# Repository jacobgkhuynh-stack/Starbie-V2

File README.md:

Hiya, this is for Half Life week 1 it's a Starbie: basically a desktop Tamagotchi but I made it into a compact rectangle creatively named the Starbie V2. How a Starbie works is it's basically the same thing as a Tamagotchi but you can tilt and move it to also interact with it.
So it has a 0.96in 128x64 oled display, a XIAO-ESP32-C3 as the brain, a DHT11 for temp and humidity sensing, and a MPU6050 for motion tracking.

Here's my BoMs
 Part | What it's for | Qty | Unit | Total | Vendor |
| --- | --- | --- | --- | --- | --- |
| [XIAO ESP32-C3](https://www.aliexpress.us/item/3256808627180483.html?spm=a2g0o.productlist.main.48.e3a850f6qPDWIA&algo_pvid=2e0f51a2-6e46-4c0e-9cd4-9e7c8a9bc2bc&algo_exp_id=2e0f51a2-6e46-4c0e-9cd4-9e7c8a9bc2bc-45&pdp_ext_f=%7B%22order%22%3A%22425%22%2C%22eval%22%3A%221%22%2C%22fromPage%22%3A%22search%22%7D&pdp_npi=6%40dis%21USD%2133.87%219.42%21%21%21225.63%2162.75%21%402101ca8b17917712554883951e117a%2112000046840040808%21sea%21US%210%21ABX%211%210%21n_tag%3A-29910%3Bd%3A92917014%3Bm03_new_user%3A-29895%3BpisId%3A5000000218165385&curPageLogUid=uNjXBfIDAfCY&utparam-url=scene%3Asearch%7Cquery_from%3A%7Cx_object_id%3A1005008813495235%7C_p_origin_prod%3A) | Dev board | 1 | $10.26 | $10.26 | [ANSIKI IoT Store](https://www.aliexpress.us/item/3256808627180483.html?spm=a2g0o.productlist.main.48.e3a850f6qPDWIA&algo_pvid=2e0f51a2-6e46-4c0e-9cd4-9e7c8a9bc2bc&algo_exp_id=2e0f51a2-6e46-4c0e-9cd4-9e7c8a9bc2bc-45&pdp_ext_f=%7B%22order%22%3A%22425%22%2C%22eval%22%3A%221%22%2C%22fromPage%22%3A%22search%22%7D&pdp_npi=6%40dis%21USD%2133.87%219.42%21%21%21225.63%2162.75%21%402101ca8b17917712554883951e117a%2112000046840040808%21sea%21US%210%21ABX%211%210%21n_tag%3A-29910%3Bd%3A92917014%3Bm03_new_user%3A-29895%3BpisId%3A5000000218165385&curPageLogUid=uNjXBfIDAfCY&utparam-url=scene%3Asearch%7Cquery_from%3A%7Cx_object_id%3A1005008813495235%7C_p_origin_prod%3A) |
| [50 PCS resistor 10k Ω](https://www.aliexpress.us/item/3256807158737978.html?spm=a2g0o.productlist.main.5.5b332a0aaNSTxm&algo_pvid=2ca68e9f-f39e-4a55-baa2-610068247927&algo_exp_id=2ca68e9f-f39e-4a55-baa2-610068247927-4&pdp_ext_f=%7B%22order%22%3A%227827%22%2C%22eval%22%3A%221%22%2C%22orig_sl_item_id%22%3A%221005007345052730%22%2C%22orig_item_id%22%3A%221005007010335100%22%2C%22fromPage%22%3A%22search%22%7D&pdp_npi=6%40dis%21USD%212.82%211.41%21%21%2118.76%219.38%21%402101d9ef17917715766673455e0ccd%2112000040354424608%21sea%21US%210%21ABX%211%210%21n_tag%3A-29910%3Bd%3A92917014%3Bm03_new_user%3A-29895&curPageLogUid=0ynae3uZRRjr&utparam-url=scene%3Asearch%7Cquery_from%3A%7Cx_object_id%3A1005007345052730%7C_p_origin_prod%3A1005007010335100) | One resistor on the DHT11 data pin | 1 | $1.41 | $1.41 | [YXSHENG Choice Store](https://www.aliexpress.us/item/3256807158737978.html?spm=a2g0o.productlist.main.5.5b332a0aaNSTxm&algo_pvid=2ca68e9f-f39e-4a55-baa2-610068247927&algo_exp_id=2ca68e9f-f39e-4a55-baa2-610068247927-4&pdp_ext_f=%7B%22order%22%3A%227827%22%2C%22eval%22%3A%221%22%2C%22orig_sl_item_id%22%3A%221005007345052730%22%2C%22orig_item_id%22%3A%221005007010335100%22%2C%22fromPage%22%3A%22search%22%7D&pdp_npi=6%40dis%21USD%212.82%211.41%21%21%2118.76%219.38%21%402101d9ef17917715766673455e0ccd%2112000040354424608%21sea%21US%210%21ABX%211%210%21n_tag%3A-29910%3Bd%3A92917014%3Bm03_new_user%3A-29895&curPageLogUid=0ynae3uZRRjr&utparam-url=scene%3Asearch%7Cquery_from%3A%7Cx_object_id%3A1005007345052730%7C_p_origin_prod%3A1005007010335100) |
| [4 pcs Gateron Milky Pro Yellow Red Switches](https://www.aliexpress.us/item/3256806853058204.html?spm=a2g0o.detail.similar_items.2.1fb7HBH7HBH7lZ&utparam-url=scene%3Aimage_search%7Cquery_from%3Aapp_pdp_sold_out%7Cx_object_id%3A1005007039372956%7C_p_origin_prod%3A&algo_pvid=db712eb1-56d9-4e91-86e1-a400e9c1582b&algo_exp_id=db712eb1-56d9-4e91-86e1-a400e9c1582b&pdp_ext_f=%7B%22order%22%3A%22189%22%2C%22fromPage%22%3A%22search%22%7D&pdp_npi=6%40dis%21USD%215.96%215.26%21%21%2139.74%2135.10%21%4021033b3317917720254308919e0e5d%2112000039183612475%21sea%21US%210%21ABX%211%210%21n_tag%3A-29910%3Bd%3A92917014%3Bm03_new_user%3A-29895%3BpisId%3A5000000219058484&gatewayAdapt=4itemAdapt) | Pressing button on my tamagochi | 1 | $5.96 | $5.96 | [ZS Enterprise Store](https://www.aliexpress.us/item/3256806853058204.html?spm=a2g0o.detail.similar_items.2.1fb7HBH7HBH7lZ&utparam-url=scene%3Aimage_search%7Cquery_from%3Aapp_pdp_sold_out%7Cx_object_id%3A1005007039372956%7C_p_origin_prod%3A&algo_pvid=db712eb1-56d9-4e91-86e1-a400e9c1582b&algo_exp_id=db712eb1-56d9-4e91-86e1-a400e9c1582b&pdp_ext_f=%7B%22order%22%3A%22189%22%2C%22fromPage%22%3A%22search%22%7D&pdp_npi=6%40dis%21USD%215.96%215.26%21%21%2139.74%2135.10%21%4021033b3317917720254308919e0e5d%2112000039183612475%21sea%21US%210%21ABX%211%210%21n_tag%3A-29910%3Bd%3A92917014%3Bm03_new_user%3A-29895%3BpisId%3A5000000219058484&gatewayAdapt=4itemAdapt) |
| [MPU6050](https://www.aliexpress.us/item/3256812536361672.html?spm=a2g0o.productlist.main.4.3bb33357uTh15i&aem_p4p_detail=202610111930152402438721507840002595886&algo_pvid=ca895bb3-2a50-496a-a9d0-2d9bbd1d1345&algo_exp_id=ca895bb3-2a50-496a-a9d0-2d9bbd1d1345-3&pdp_ext_f=%7B%22order%22%3A%22273%22%2C%22eval%22%3A%221%22%2C%22fromPage%22%3A%22search%22%7D&pdp_npi=6%40dis%21USD%213.86%211.09%21%21%2125.73%217.28%21%402101e5ab17917722150867071e0ddb%2112000059167286842%21sea%21US%210%21ABX%211%210%21n_tag%3A-29910%3Bd%3A92917014%3Bm03_new_user%3A-29895%3BpisId%3A5000000218165385&curPageLogUid=akFypNxLNwqu&utparam-url=scene%3Asearch%7Cquery_from%3A%7Cx_object_id%3A1005012722676424%7C_p_origin_prod%3A&search_p4p_id=202610111930152402438721507840002595886_1) | Movement sensing | 1 | $3.86 | $3.86 | [Nextronics Store](https://www.aliexpress.us/item/3256812536361672.html?spm=a2g0o.productlist.main.4.3bb33357uTh15i&aem_p4p_detail=202610111930152402438721507840002595886&algo_pvid=ca895bb3-2a50-496a-a9d0-2d9bbd1d1345&algo_exp_id=ca895bb3-2a50-496a-a9d0-2d9bbd1d1345-3&pdp_ext_f=%7B%22order%22%3A%22273%22%2C%22eval%22%3A%221%22%2C%22fromPage%22%3A%22search%22%7D&pdp_npi=6%40dis%21USD%213.86%211.09%21%21%2125.73%217.28%21%402101e5ab17917722150867071e0ddb%2112000059167286842%21sea%21US%210%21ABX%211%210%21n_tag%3A-29910%3Bd%3A92917014%3Bm03_new_user%3A-29895%3BpisId%3A5000000218165385&curPageLogUid=akFypNxLNwqu&utparam-url=scene%3Asearch%7Cquery_from%3A%7Cx_object_id%3A1005012722676424%7C_p_origin_prod%3A&search_p4p_id=202610111930152402438721507840002595886_1) |
| [SSD1306 OLED Display](https://www.aliexpress.us/item/3256805954920554.html?spm=a2g0o.productlist.main.3.83af198b8AM3LX&algo_pvid=41b1f5ff-3551-4827-848e-900b5064ba63&algo_exp_id=41b1f5ff-3551-4827-848e-900b5064ba63-2&pdp_ext_f=%7B%22order%22%3A%2226455%22%2C%22eval%22%3A%221%22%2C%22fromPage%22%3A%22search%22%7D&pdp_npi=6%40dis%21USD%212.78%211.09%21%21%2118.49%217.23%21%4021033b3317917729422134662e0fc8%2112000035944225407%21sea%21US%210%21ABX%211%210%21n_tag%3A-29910%3Bd%3A92917014%3Bm03_new_user%3A-29895%3BpisId%3A5000000218032551&curPageLogUid=7qPcByhLGPs4&utparam-url=scene%3Asearch%7Cquery_from%3A%7Cx_object_id%3A1005006141235306%7C_p_origin_prod%3A) | Displaying my pet | 1 | $2.78 | $2.78 | [YouKeyi Store](https://www.aliexpress.us/item/3256805954920554.html?spm=a2g0o.productlist.main.3.83af198b8AM3LX&algo_pvid=41b1f5ff-3551-4827-848e-900b5064ba63&algo_exp_id=41b1f5ff-3551-4827-848e-900b5064ba63-2&pdp_ext_f=%7B%22order%22%3A%2226455%22%2C%22eval%22%3A%221%22%2C%22fromPage%22%3A%22search%22%7D&pdp_npi=6%40dis%21USD%212.78%211.09%21%21%2118.49%217.23%21%4021033b3317917729422134662e0fc8%2112000035944225407%21sea%21US%210%21ABX%211%210%21n_tag%3A-29910%3Bd%3A92917014%3Bm03_new_user%3A-29895%3BpisId%3A5000000218032551&curPageLogUid=7qPcByhLGPs4&utparam-url=scene%3Asearch%7Cquery_from%3A%7Cx_object_id%3A1005006141235306%7C_p_origin_prod%3A) |
| [DHT11](https://www.aliexpress.us/item/3256808767116188.html?spm=a2g0o.productlist.main.8.53ff71f3SWSGMK&aem_p4p_detail=202610111934044683110678197680002567119&algo_pvid=64f6cf29-2f46-449a-aa2b-7fca47de3b3f&algo_exp_id=64f6cf29-2f46-449a-aa2b-7fca47de3b3f-7&pdp_ext_f=%7B%22order%22%3A%22241%22%2C%22eval%22%3A%221%22%2C%22fromPage%22%3A%22search%22%7D&pdp_npi=6%40dis%21USD%211.78%211.09%21%21%2111.83%217.23%21%402101ca9517917724444004141e12b4%2112000047346503744%21sea%21US%210%21ABX%211%210%21n_tag%3A-29910%3Bd%3A92917014%3Bm03_new_user%3A-29895%3BpisId%3A5000000218165385&curPageLogUid=MNq6t5mbC4St&utparam-url=scene%3Asearch%7Cquery_from%3A%7Cx_object_id%3A1005008953430940%7C_p_origin_prod%3A&search_p4p_id=202610111934044683110678197680002567119_2) | Temp and Humdity sensing | 1 | $1.78 | $1.78 | [Good Luck Electronic Products Store](https://www.aliexpress.us/item/3256808767116188.html?spm=a2g0o.productlist.main.8.53ff71f3SWSGMK&aem_p4p_detail=202610111934044683110678197680002567119&algo_pvid=64f6cf29-2f46-449a-aa2b-7fca47de3b3f&algo_exp_id=64f6cf29-2f46-449a-aa2b-7fca47de3b3f-7&pdp_ext_f=%7B%22order%22%3A%22241%22%2C%22eval%22%3A%221%22%2C%22fromPage%22%3A%22search%22%7D&pdp_npi=6%40dis%21USD%211.78%211.09%21%21%2111.83%217.23%21%402101ca9517917724444004141e12b4%2112000047346503744%21sea%21US%210%21ABX%211%210%21n_tag%3A-29910%3Bd%3A92917014%3Bm03_new_user%3A-29895%3BpisId%3A5000000218165385&curPageLogUid=MNq6t5mbC4St&utparam-url=scene%3Asearch%7Cquery_from%3A%7Cx_object_id%3A1005008953430940%7C_p_origin_prod%3A&search_p4p_id=202610111934044683110678197680002567119_2) |
| [PCB](https://jlcpcb.com) | Connecting everything | 1 | $1.50 | $1.50 | [JLCPCB](https://jlcpcb.com) |
| **Parts subtotal** | — | — | — | **$27.55** | — |
| **Tax & shipping** | — | — | — | **$3.13** | — |
| **Total** | — | — | — | **$30.68** | — |

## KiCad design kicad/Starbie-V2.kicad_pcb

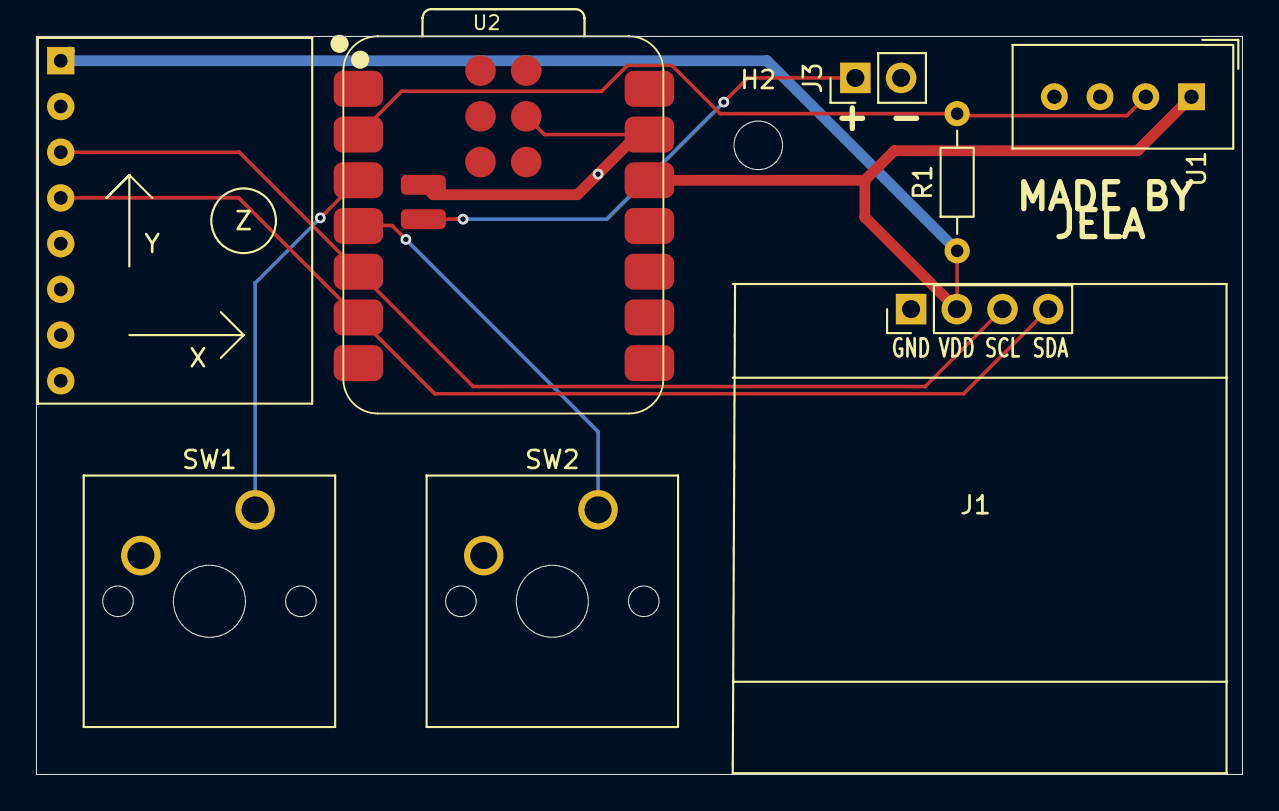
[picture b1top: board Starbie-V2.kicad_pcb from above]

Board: 2 copper layers, 67.0 x 41.0 mm, 9 parts (0 on the bottom side), 8 nets.

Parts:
H2: MountingHole; MountingHole_2.7mm_M2.5
J1: Conn_01x04_Pin; Display_128x64_096_I2C
J2: Conn_01x08_Pin; MPU6050_Module
J3: Conn_01x02_Pin; PinHeader_1x02_P2.54mm_Vertical
R1: 10k; R_Axial_DIN0204_L3.6mm_D1.6mm_P7.62mm_Horizontal
SW1, SW2: SW_Push; SW_Cherry_MX_1.00u_PCB
U1: DHT11; Aosong_DHT11_5.5x12.0_P2.54mm
U2: XIAO-ESP32-C3-SMD

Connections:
+3.3V: J1.2, J2.1, R1.1, U1.1 (VDD), U2.12 (3V3_OUT)
/DHT11 DATA: R1.2, U1.2 (DATA), U2.2 (D1)
/GPIO2: SW1.1, U2.3 (D2)
/GPIO3: SW2.1, U2.4 (D3)
/SCL: J1.3, J2.3, U2.5 (D4)
/SDA: J1.4, J2.4, U2.6 (D5)
GND: J1.1, J2.2, J3.2, SW1.2, SW2.2, U1.4 (GND), U2.13 (GND), U2.18 (GND), U2.22 (GND)
unnamed: J3.1, U2.21 (VBAT)
